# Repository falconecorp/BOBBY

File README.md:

# BOBBY
Bobby es un robot construido para competir en los juegos bonaerenses, en la categoría de Triatlón( Quita obstaculos - Sumo - Seguidor de linea ), por los estudiantes, Iago Botto, Dante Abel Canale, Lautaro Lammers y Lucas Chavez

[img_20240703_164955.md](https://github.com/user-attachments/files/17923314/img_20240703_164955.md)

## FUNCIONAMIENTO

### Seguidor de linea:
  Tenemos un sistema de sensores reflectivos QRE1113GR, en configuracion de array, que permite detectar con precisión, una linea blanca que representa el camino, y debemos recorrerlo en el menor tiempo posible
Utilizamos un algorimo de PD
~~~
  uint8_t PID(){
    int error = setpoint - lecturaQRE();
    int P = error * Kp;
    int D = (error - ultimo_error) * Kd;
    ultimo_error = error;
    float output = P + D;
    output = abs(output);
    output = map(output, 0, 25000, 0, limite_output);
    output = constrain(output, 0, limite_output);
    return (output);
  }
~~~
que nos permite poder variar los valores PWM enviados al motor, para seguir la linea correctamente

### Quita Obstáculos
  Nos encontramos con 5 sensores GP2Y0A02YK0F de distancia, que con un algoritmo y filtro digital, verificamos si hay un objeto o no. Agregado a esto, se utilizan 3 sensores de piso QRE1113GR, para evitar caernos de la pista
cuando atacamos a cada obstáculo.

### Sumo
  Aqui tenemos a nuestra categoría estrella, en esta disciplina, el robot es controlado por el usuario a través de una conexión Bluetooth entre un joystick de Ps3, y un modulo ESP32. Se compite contra otro robot en las mismas condiciones en un tatami.

## INFORME DE COSTES
#### Sensores
  -Sharp GP2Y0A02YK0F: 10.509$ c/u (starware)  (x5)    
  -Sensores de piso QRE1113GR: 969.37$ c/u (mouser)  (x8)    
  -impresion 3D: 8.000$ (300 gr)    
  -Motores AP&S SP6-260: 26.000$ c/u (AP&S)  (x2)    
  -Controladores BTS7960: 20.0000$ c/u (MercadoLibre)  (x2)    
  -ESP32: 7.329$ c/u (Starware)   (x1)    
  -Conexionado y cables: 20.000$ (it&t)    
#### Costo total: 187.626$
## FALLAS Y COSAS A MEJORAR
### organización
  -Problemas en el cálculo de tiempos.    
  -incumplimientos de los plazos acordados.    
  -falta de compromiso con el proyecto.    
  -falta de conocimientos previos para un proyecto de este calibre.    
  -subestimacion de los demas competidores.    

### programación
  Sumo: no hubo problemas mayores.    
  Seguidor de linea:    
    - dificultades a la hora de modificar valores de PID y varios.    
    - eleccion de sensores que complicaron las pruebas(QRE1113GR) necesita una distancia con respecto al piso muy pequeña.    
  Quita Obstáculos:    
    - no dedicarle tiempo a esta disciplina, lo que nos puso en desventaja con respecto a los otros.    
    - problemas en la estructura de manejo de sensores.    
    - problemas en la detección del limite de pista, debido a la altura incorrecta de los QRE1113GR

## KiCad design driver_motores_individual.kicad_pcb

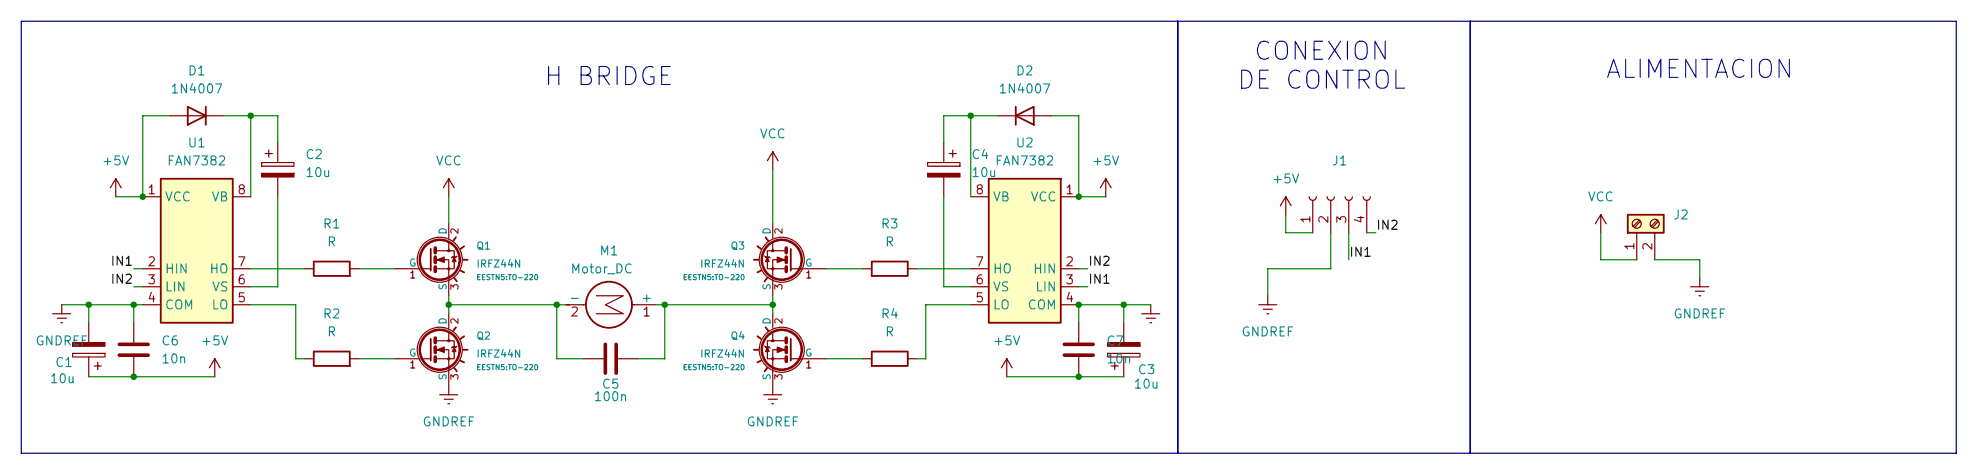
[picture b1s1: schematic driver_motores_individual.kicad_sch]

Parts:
C1, C2, C3, C4: 10u; C_0805_2012Metric_Pad1.18x1.45mm_HandSolder
C5: 100n; C_Disc_D4.7mm_W2.5mm_P5.00mm
C6, C7: 10n
D1, D2: 1N4007; D_0805_2012Metric_Pad1.15x1.40mm_HandSolder
J1: CONEXIÓN DE CONTROL; pin_strip_4
J2: Screw_Terminal_01x02; BORNERA2_AZUL
M1: Motor_DC; BORNERA2_AZUL
Q1, Q2, Q3, Q4: IRFZ44N; TO-220
R1, R2, R3, R4: R; R_0805_2012Metric_Pad1.20x1.40mm_HandSolder
U1, U2: FAN7382; DIP-8

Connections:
+5V: C1.1, C3.1, C6.2, C7.2, D1.2 (A), D2.2 (A), J1.1, U1.1 (VCC), U2.1 (VCC)
/IN1: J1.3, U1.2 (HIN), U2.3 (LIN)
/IN2: J1.4, U1.3 (LIN), U2.2 (HIN)
GNDREF: C1.2, C3.2, C6.1, C7.1, J1.2, J2.2, Q2.3 (S), Q4.3 (S), U1.4 (COM), U2.4 (COM)
unnamed: C2.1, D1.1 (K), U1.8 (VB)
unnamed: C4.1, D2.1 (K), U2.8 (VB)
unnamed: C5.1, M1.1 (+), Q3.3 (S), Q4.2 (D)
unnamed: C5.2, M1.2 (-), Q1.3 (S), Q2.2 (D)
unnamed: Q1.1 (G), R1.2
unnamed: Q2.1 (G), R2.2
unnamed: Q3.1 (G), R3.2
unnamed: Q4.1 (G), R4.2
unnamed: R1.1, U1.7 (HO)
unnamed: R2.1, U1.5 (LO)
unnamed: C2.2, U1.6 (VS)
unnamed: R3.1, U2.7 (HO)
unnamed: R4.1, U2.5 (LO)
unnamed: C4.2, U2.6 (VS)
VCC: J2.1, Q1.2 (D), Q3.2 (D)

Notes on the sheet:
ALIMENTACION
H BRIDGE
CONEXION DE CONTROL

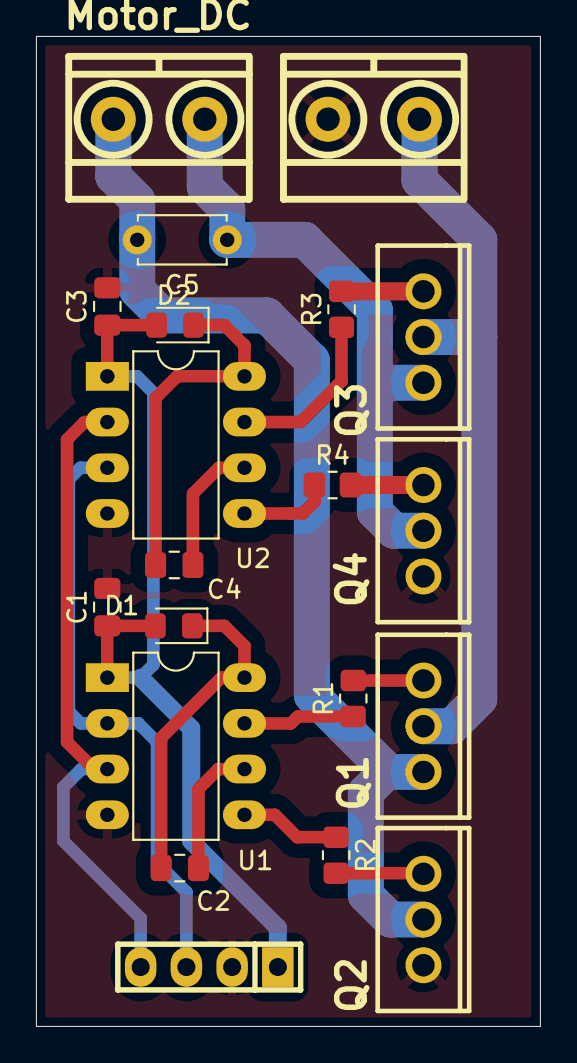
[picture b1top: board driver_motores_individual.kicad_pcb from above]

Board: 2 copper layers, 28.0 x 55.0 mm, 20 parts (0 on the bottom side), 19 nets.

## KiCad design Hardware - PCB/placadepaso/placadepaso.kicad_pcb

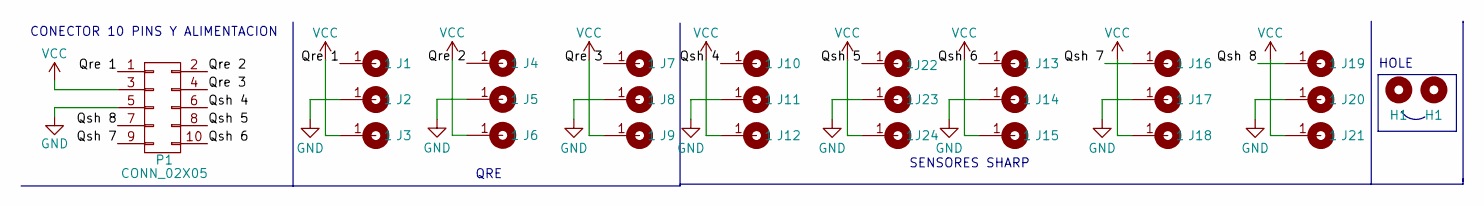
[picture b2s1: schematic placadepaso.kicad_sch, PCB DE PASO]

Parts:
H1: Mounting_Hole; Tornillo_M3_8mm
J1, J2, J3, J4, J5, J6, J7, J8, J9, J10, J11, J12, J13, J14, J15, J16, J17, J18, J19, J20, J21, J22, J23, J24: Cable_PAD; Cable_Doble_1,5mm_little
P1: CONN_02X05; Header_2x05x2.54mm_Vertical

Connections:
/Qre 1: J1.1, P1.1
/Qre 2: J4.1, P1.2
/Qre 3: J7.1, P1.4
/Qsh 4: J10.1, P1.6
/Qsh 5: J22.1, P1.8
/Qsh 6: J13.1, P1.10
/Qsh 7: J16.1, P1.9
/Qsh 8: J19.1, P1.7
GND: J2.1, J5.1, J8.1, J11.1, J14.1, J17.1, J20.1, J23.1, P1.5
VCC: J3.1, J6.1, J9.1, J12.1, J15.1, J18.1, J21.1, J24.1, P1.3

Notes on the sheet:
HOLE
QRE
CONECTOR 10 PINS Y ALIMENTACION
SENSORES SHARP

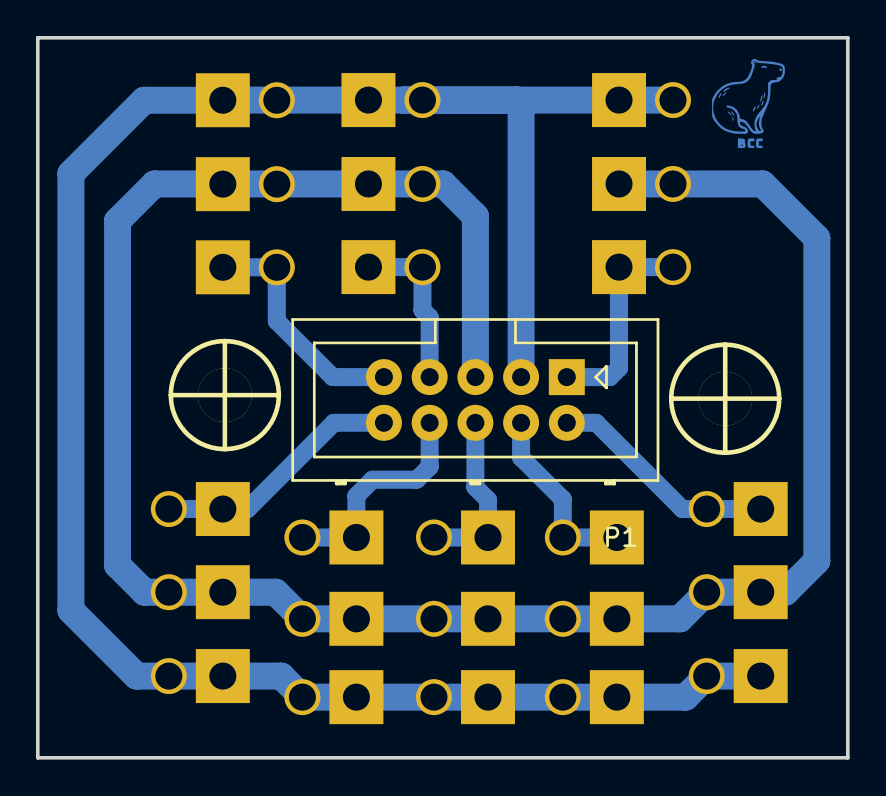
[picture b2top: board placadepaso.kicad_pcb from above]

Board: 2 copper layers, 45.0 x 40.0 mm, 27 parts (0 on the bottom side), 10 nets.

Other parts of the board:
H2: Mounting_Hole; Tornillo_M3_8mm

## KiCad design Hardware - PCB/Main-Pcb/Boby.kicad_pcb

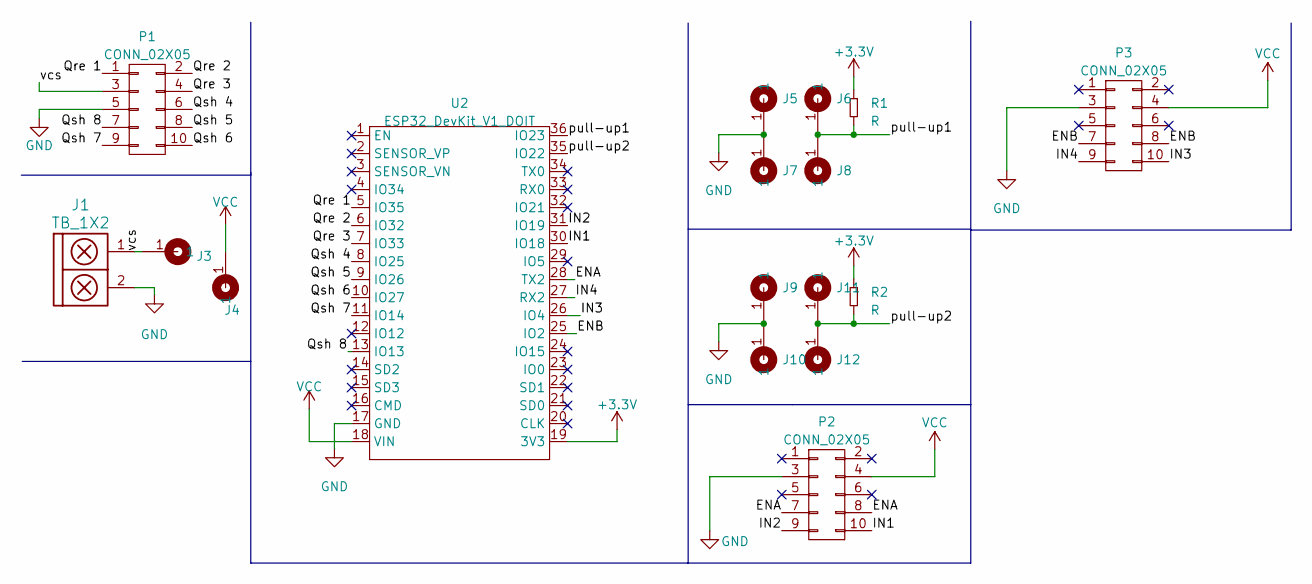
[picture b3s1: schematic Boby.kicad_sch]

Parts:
J1: TB_1X2; BORNERA2_AZUL
J3, J4: Cable_PAD; Cable_1,5mm
J5, J6, J7, J8, J9, J10, J11, J12: Cable_PAD; Cable_Doble_1,5mm_little
P1, P2, P3: CONN_02X05; Header_2x05x2.54mm_Vertical
R1, R2: R; RES0.3
U2: ESP32_DevKit_V1_DOIT; ESP32_DEVKIT_V1_DOIT

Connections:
+3.3V: R1.1, R2.1, U2.19 (3V3)
/ENA: P2.7, P2.8, U2.28 (TX2)
/ENB: P3.7, P3.8, U2.25 (IO2)
/IN1: P2.10, U2.30 (IO18)
/IN2: P2.9, U2.31 (IO19)
/IN3: P3.10, U2.26 (IO4)
/IN4: P3.9, U2.27 (RX2)
/Qre 1: P1.1, U2.5 (IO35)
/Qre 2: P1.2, U2.6 (IO32)
/Qre 3: P1.4, U2.7 (IO33)
/Qsh 4: P1.6, U2.8 (IO25)
/Qsh 5: P1.8, U2.9 (IO26)
/Qsh 6: P1.10, U2.10 (IO27)
/Qsh 7: P1.9, U2.11 (IO14)
/Qsh 8: P1.7, U2.13 (IO13)
/pull-up1: J6.1, J8.1, R1.2, U2.36 (IO23)
/pull-up2: J11.1, J12.1, R2.2, U2.35 (IO22)
/vcs: J1.1, J3.1, P1.3
GND: J1.2, J5.1, J7.1, J9.1, J10.1, P1.5, P2.3, P3.3, U2.17 (GND)
VCC: J4.1, P2.4, P3.4, U2.18 (VIN)

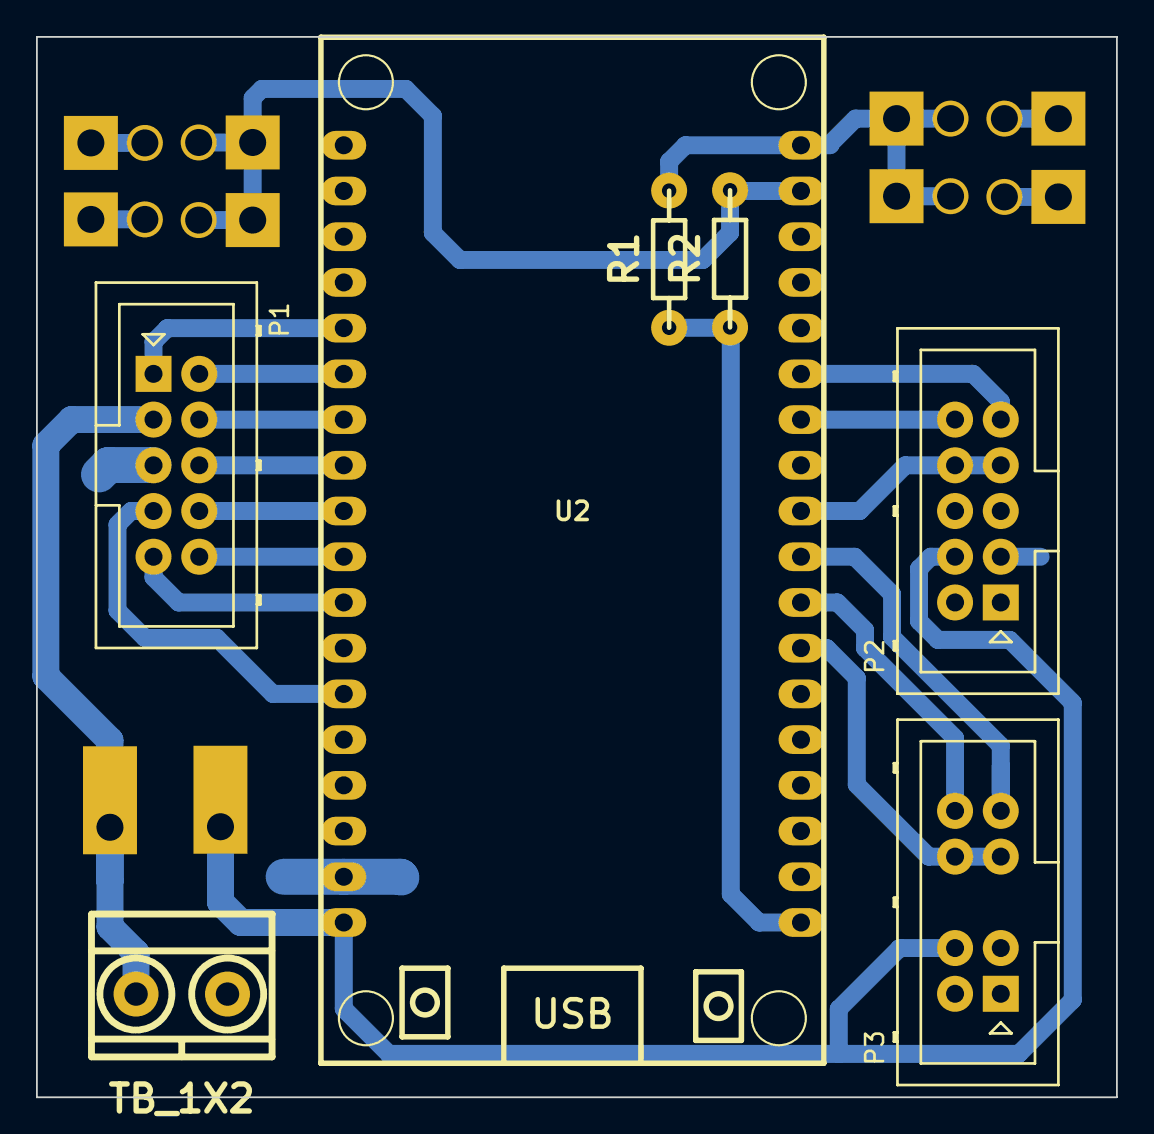
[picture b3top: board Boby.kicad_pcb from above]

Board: 2 copper layers, 60.0 x 58.9 mm, 17 parts (0 on the bottom side), 20 nets.

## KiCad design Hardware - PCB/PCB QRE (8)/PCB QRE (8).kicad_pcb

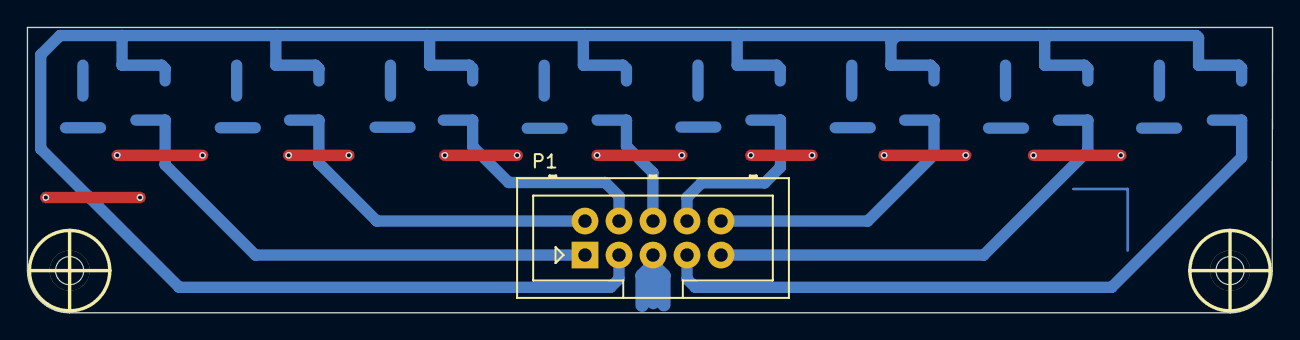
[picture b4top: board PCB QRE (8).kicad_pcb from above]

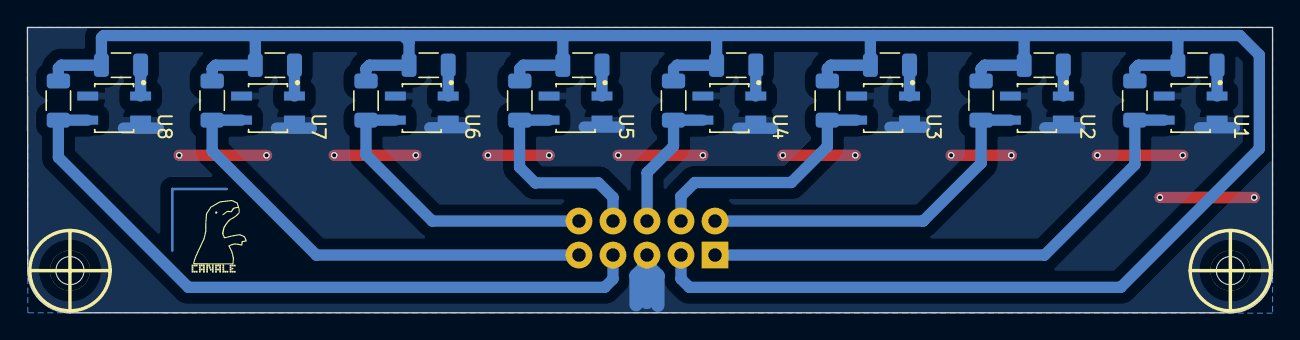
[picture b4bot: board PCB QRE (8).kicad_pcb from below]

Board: 2 copper layers, 93.0 x 21.3 mm, 29 parts (24 on the bottom side), 18 nets.

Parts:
H1, H2: Mounting_Hole; MountingHole_2.1mm
P1: CONN_02X05; Header_2x05x2.54mm_Vertical
R1, R3, R5, R7, R9, R11, R13, R15: 100; R_1206_3216Metric
R2, R4, R6, R8, R10, R12, R14, R16: 240; R_1206_3216Metric
U1, U2, U3, U4, U5, U6, U7, U8: QRE1113GR; SOIC180P460X187-4N
hole_3mm, hole_3mm#2: VAL**; hole_3mm

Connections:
/PIN1: P1.1, R2.1, U1.3
/PIN2: P1.2, R4.1, U2.3
/PIN3: P1.4, R6.1, U3.3
/PIN4: P1.6, R8.1, U4.3
/PIN5: P1.8, R10.1, U5.3
/PIN6: P1.10, R12.1, U6.3
/PIN7: P1.9, R14.1, U7.3
/PIN8: P1.7, R16.1, U8.3
GND: P1.5, U1.2, U1.4, U2.2, U2.4, U3.2, U3.4, U4.2, U4.4, U5.2, U5.4, U6.2, U6.4, U7.2, U7.4, U8.2, U8.4
unnamed: R1.1, U1.1
unnamed: R3.1, U2.1
unnamed: R5.1, U3.1
unnamed: R7.1, U4.1
unnamed: R9.1, U5.1
unnamed: R11.1, U6.1
unnamed: R13.1, U7.1
unnamed: R15.1, U8.1
VCC: P1.3, R1.2, R2.2, R3.2, R4.2, R5.2, R6.2, R7.2, R8.2, R9.2, R10.2, R11.2, R12.2, R13.2, R14.2, R15.2, R16.2

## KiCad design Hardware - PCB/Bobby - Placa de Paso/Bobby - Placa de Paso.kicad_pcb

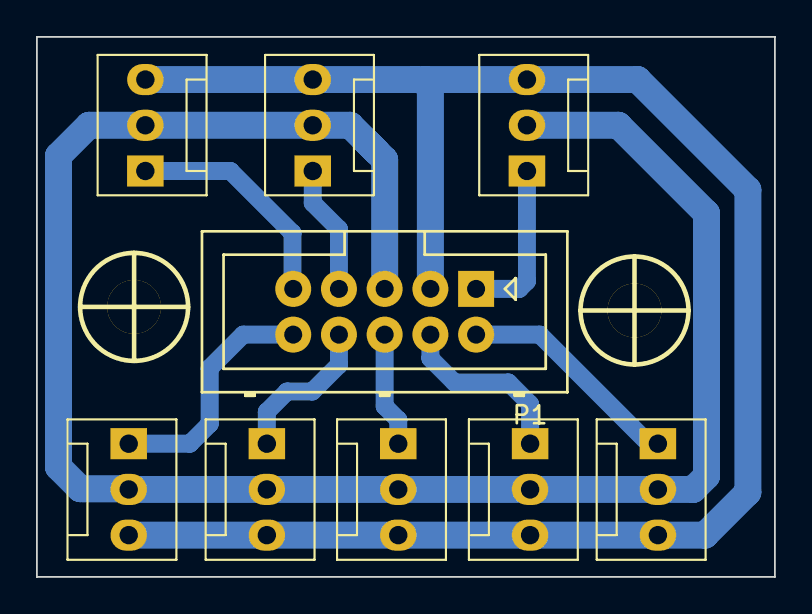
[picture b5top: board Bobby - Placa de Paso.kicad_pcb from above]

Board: 2 copper layers, 41.0 x 30.0 mm, 11 parts (0 on the bottom side), 10 nets.

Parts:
H1, H2: Mounting_Hole; Tornillo_M3_8mm
P1: CONN_02X05; Header_2x05x2.54mm_Vertical
QRE1, QRE2, QRE3: CONN_01X03; FanPinHeader_1x03_P2.54mm_Vertical
QSH4, QSH5, QSH6, QSH7, QSH8: CONN_01X03; FanPinHeader_1x03_P2.54mm_Vertical

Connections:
/Qre 1: P1.1, QRE1.1
/Qre 2: P1.2, QRE2.1
/Qre 3: P1.4, QRE3.1
/Qsh 4: P1.6, QSH4.1
/Qsh 5: P1.8, QSH5.1
/Qsh 6: P1.10, QSH6.1
/Qsh 7: P1.9, QSH7.1
/Qsh 8: P1.7, QSH8.1
GND: P1.5, QRE1.2, QRE2.2, QRE3.2, QSH4.2, QSH5.2, QSH6.2, QSH7.2, QSH8.2
VCC: P1.3, QRE1.3, QRE2.3, QRE3.3, QSH4.3, QSH5.3, QSH6.3, QSH7.3, QSH8.3

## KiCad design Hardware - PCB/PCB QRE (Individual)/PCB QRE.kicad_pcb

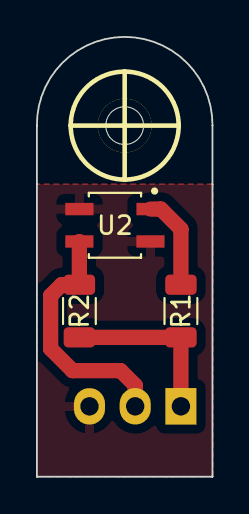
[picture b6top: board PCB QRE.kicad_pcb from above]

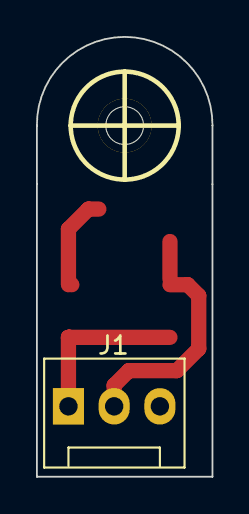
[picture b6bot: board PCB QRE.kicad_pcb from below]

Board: 2 copper layers, 9.8 x 24.4 mm, 5 parts (2 on the bottom side), 4 nets.

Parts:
J1: Conn_01X03; FanPinHeader_1x03_P2.54mm_Vertical
R1: 100; R_1206_3216Metric
R2: 240; R_1206_3216Metric
U2: QRE1113GR; SOIC180P460X187-4N
hole_3mm: VAL**; hole_3mm

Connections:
GND: J1.3, U2.2, U2.4
unnamed: J1.2, R2.1, U2.3
unnamed: R1.1, U2.1
VCC: J1.1, R1.2, R2.2

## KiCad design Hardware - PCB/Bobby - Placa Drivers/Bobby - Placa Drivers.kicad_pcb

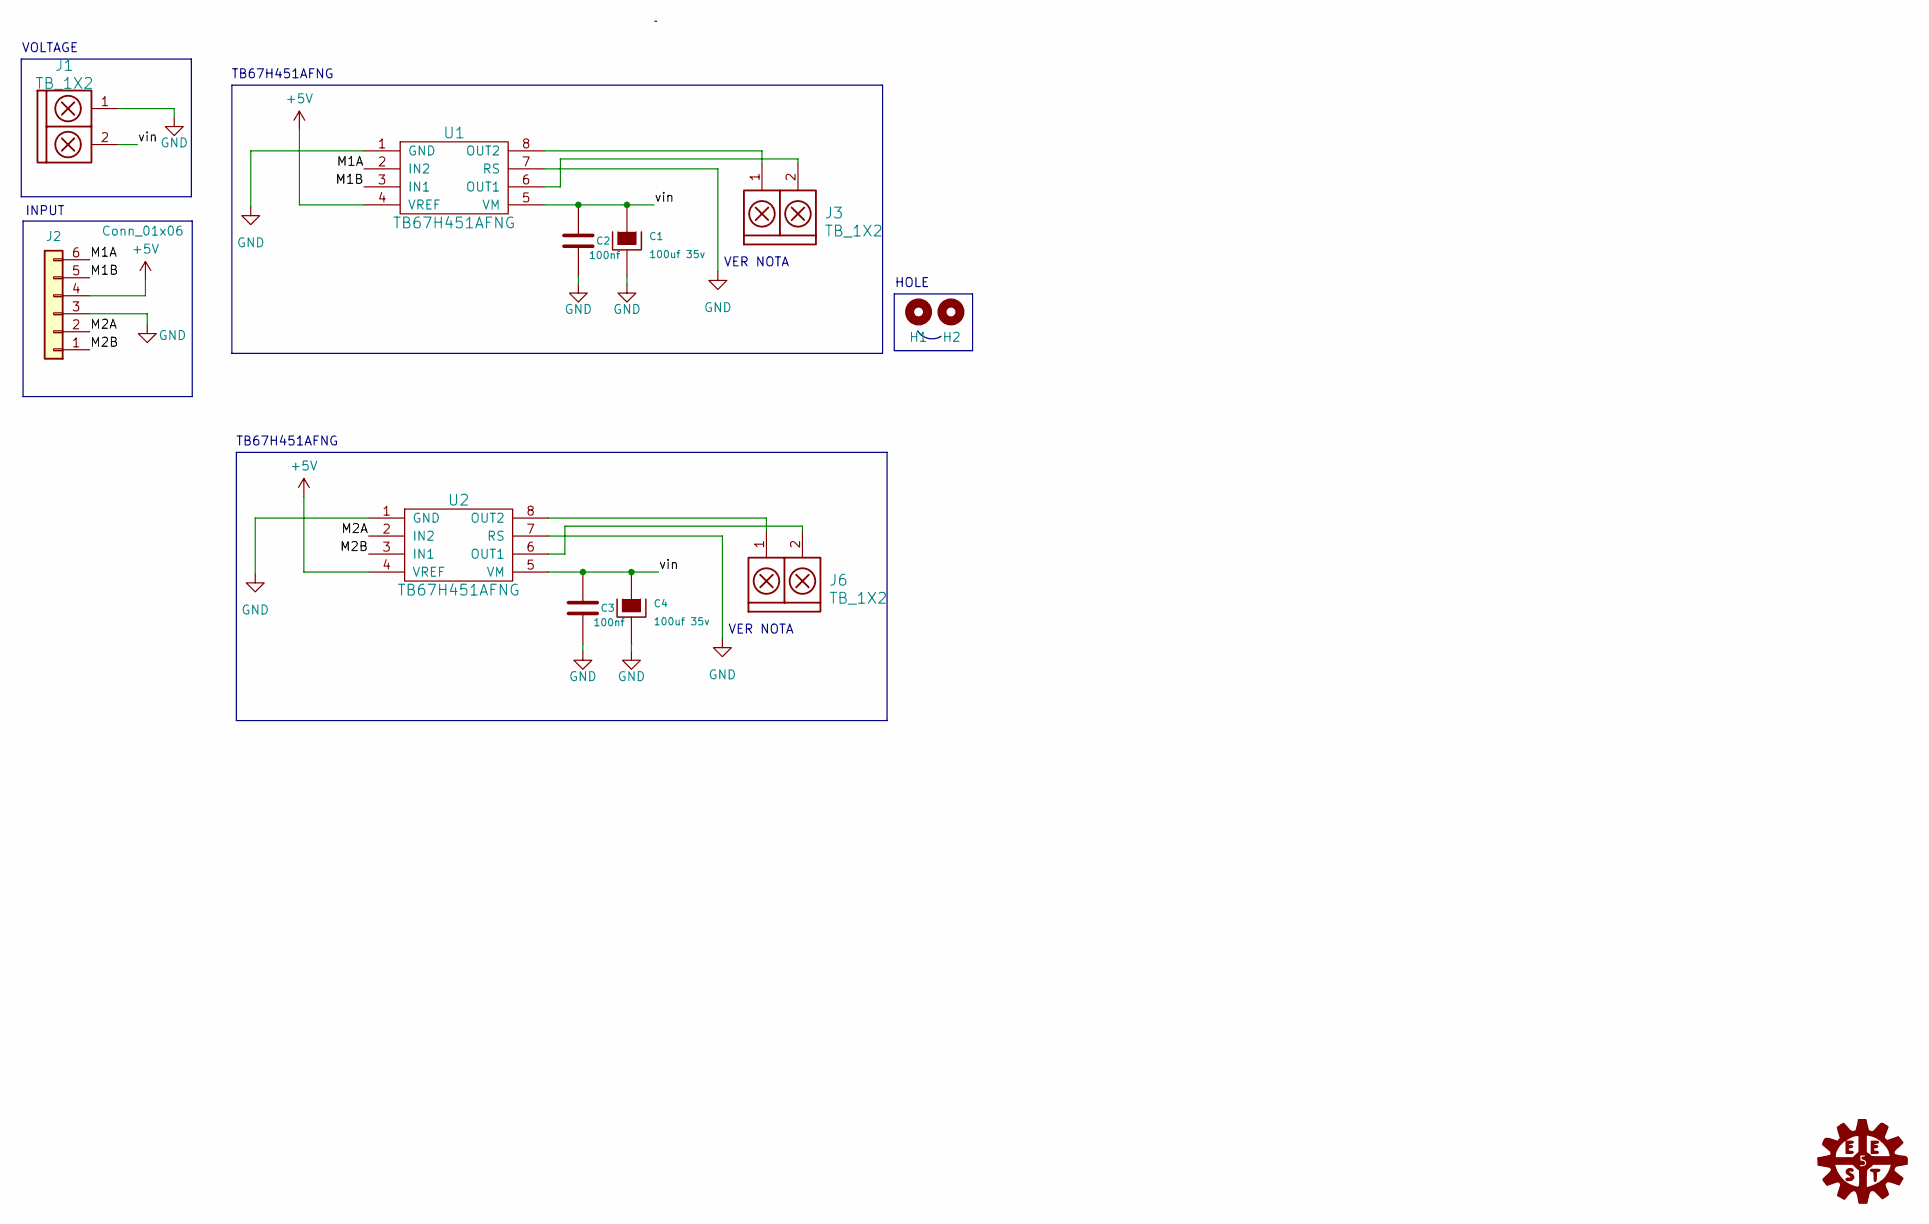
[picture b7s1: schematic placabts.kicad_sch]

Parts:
C1, C4: 100uf 35v; CAP_ELEC_10X8mm
C2, C3: 100nf; C_1206
H1, H2: Mounting_Hole; Tornillo_M3_8mm
J1, J3, J6: TB_1X2; BORNERA2_AZUL
J2: Conn_01x06; FanPinHeads_1x6_P2.54mm_Vertical
U1, U2: TB67H451AFNG; SSOP-8

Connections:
+5V: U1.4 (VREF), U2.4 (VREF); also elsewhere on the board
/M1A: U1.2 (IN2); also elsewhere on the board
/M1B: U1.3 (IN1); also elsewhere on the board
/M2A: U2.2 (IN2); also elsewhere on the board
/M2B: U2.3 (IN1); also elsewhere on the board
/vin: C1.1, C2.1, C3.1, C4.1, J1.2, U1.5 (VM), U2.5 (VM)
GND: C1.2, C2.2, C3.2, C4.2, J1.1, U1.1 (GND), U1.7 (RS), U2.1 (GND), U2.7 (RS); also elsewhere on the board
unnamed: J3.2, U1.6 (OUT1)
unnamed: J3.1, U1.8 (OUT2)
unnamed: J6.2, U2.6 (OUT1)
unnamed: J6.1, U2.8 (OUT2)

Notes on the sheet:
HOLE
VER NOTA
INPUT
TB67H451AFNG
VOLTAGE

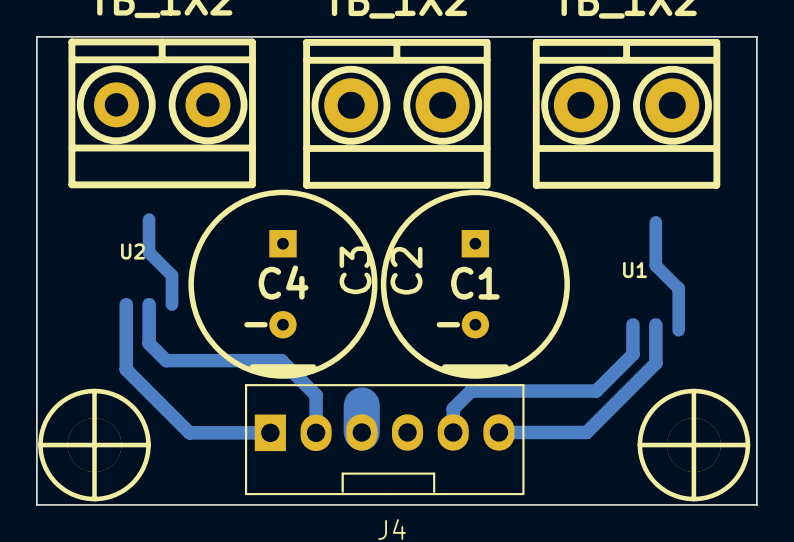
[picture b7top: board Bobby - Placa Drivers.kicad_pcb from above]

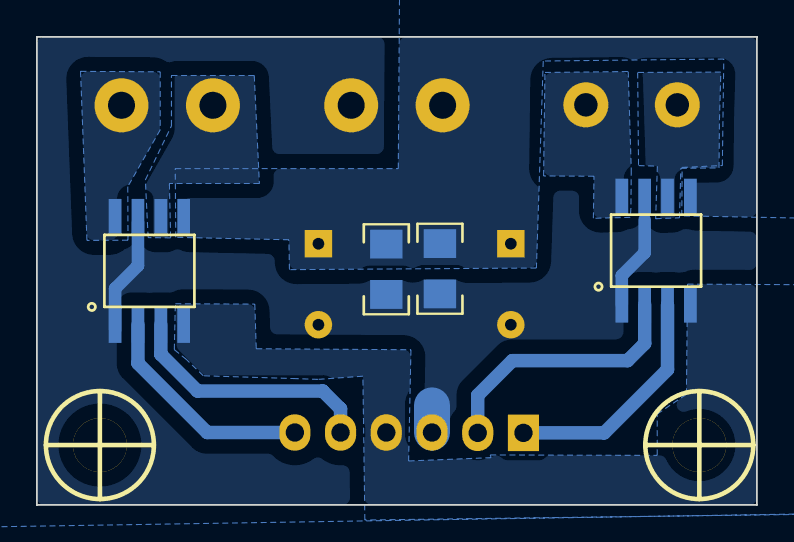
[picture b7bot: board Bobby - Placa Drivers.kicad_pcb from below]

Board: 2 copper layers, 40.0 x 26.0 mm, 12 parts (5 on the bottom side), 11 nets.

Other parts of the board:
J4: Conn_01x06; FanPinHeads_1x6_P2.54mm_Vertical

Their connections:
+5V: J4.4; also elsewhere on the board
/M1A: J4.6; also elsewhere on the board
/M1B: J4.5; also elsewhere on the board
/M2A: J4.2; also elsewhere on the board
/M2B: J4.1; also elsewhere on the board
GND: J4.3; also elsewhere on the board

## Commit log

2024-08-13 codigo y PCBs hasta el día martes 13/08
